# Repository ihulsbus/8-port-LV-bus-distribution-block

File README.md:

# Marklin-Digital-8-port-bus-distribution-block-
Schematic files for a self-made 8-port distribution block for the Märklin Digital main power &amp; data bus

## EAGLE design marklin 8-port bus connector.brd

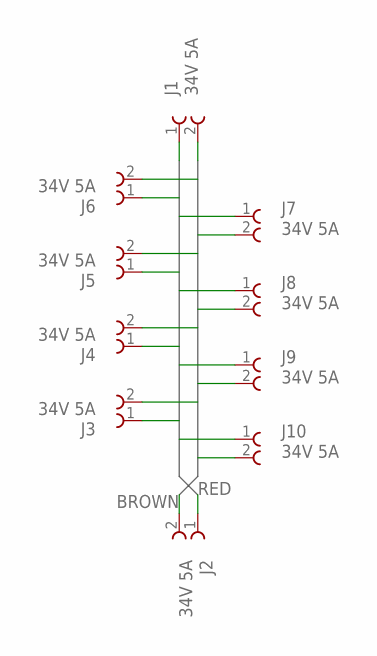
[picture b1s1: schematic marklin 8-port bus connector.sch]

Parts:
J1, J2, J3, J4, J5, J6, J7, J8, J9, J10: 34V 5A; 691111710002; MPN 691111710002

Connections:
BROWN: J1.2, J2.2, J3.2, J4.2, J5.2, J6.2, J7.2, J8.2, J9.2, J10.2
RED: J1.1, J2.1, J3.1, J4.1, J5.1, J6.1, J7.1, J8.1, J9.1, J10.1

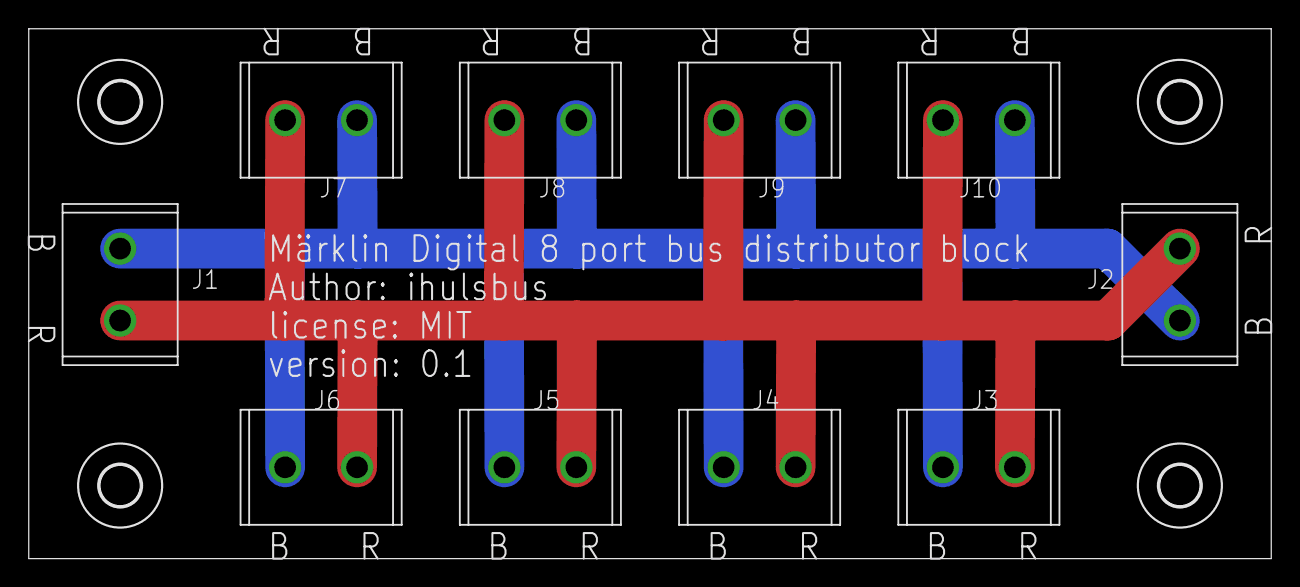
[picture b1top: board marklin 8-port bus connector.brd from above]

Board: 2 copper layers, 86.4 x 36.8 mm, 14 parts (0 on the bottom side), 2 nets.

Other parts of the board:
U$1, U$2, U$3, U$4: 2,8

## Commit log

2019-12-27 Ignore local eagle properties file
2019-12-27 Update gitignore
2019-12-27 Release version 0.1
2019-12-27 remove obsolete zip
2020-04-21 Update connectors
2021-08-23 Change LICENSE

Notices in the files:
marklin 8-port bus connector.brd:
license: MIT
parts and their libraries:
Wurth_Elektronik_Electromechanic_Termina: Copyright: Würth Elektronik
SparkFun-Aesthetics: Licensing: Creative Commons ShareAlike 4.0 International - https://creativecommons.org/licenses/by-sa/4.0
